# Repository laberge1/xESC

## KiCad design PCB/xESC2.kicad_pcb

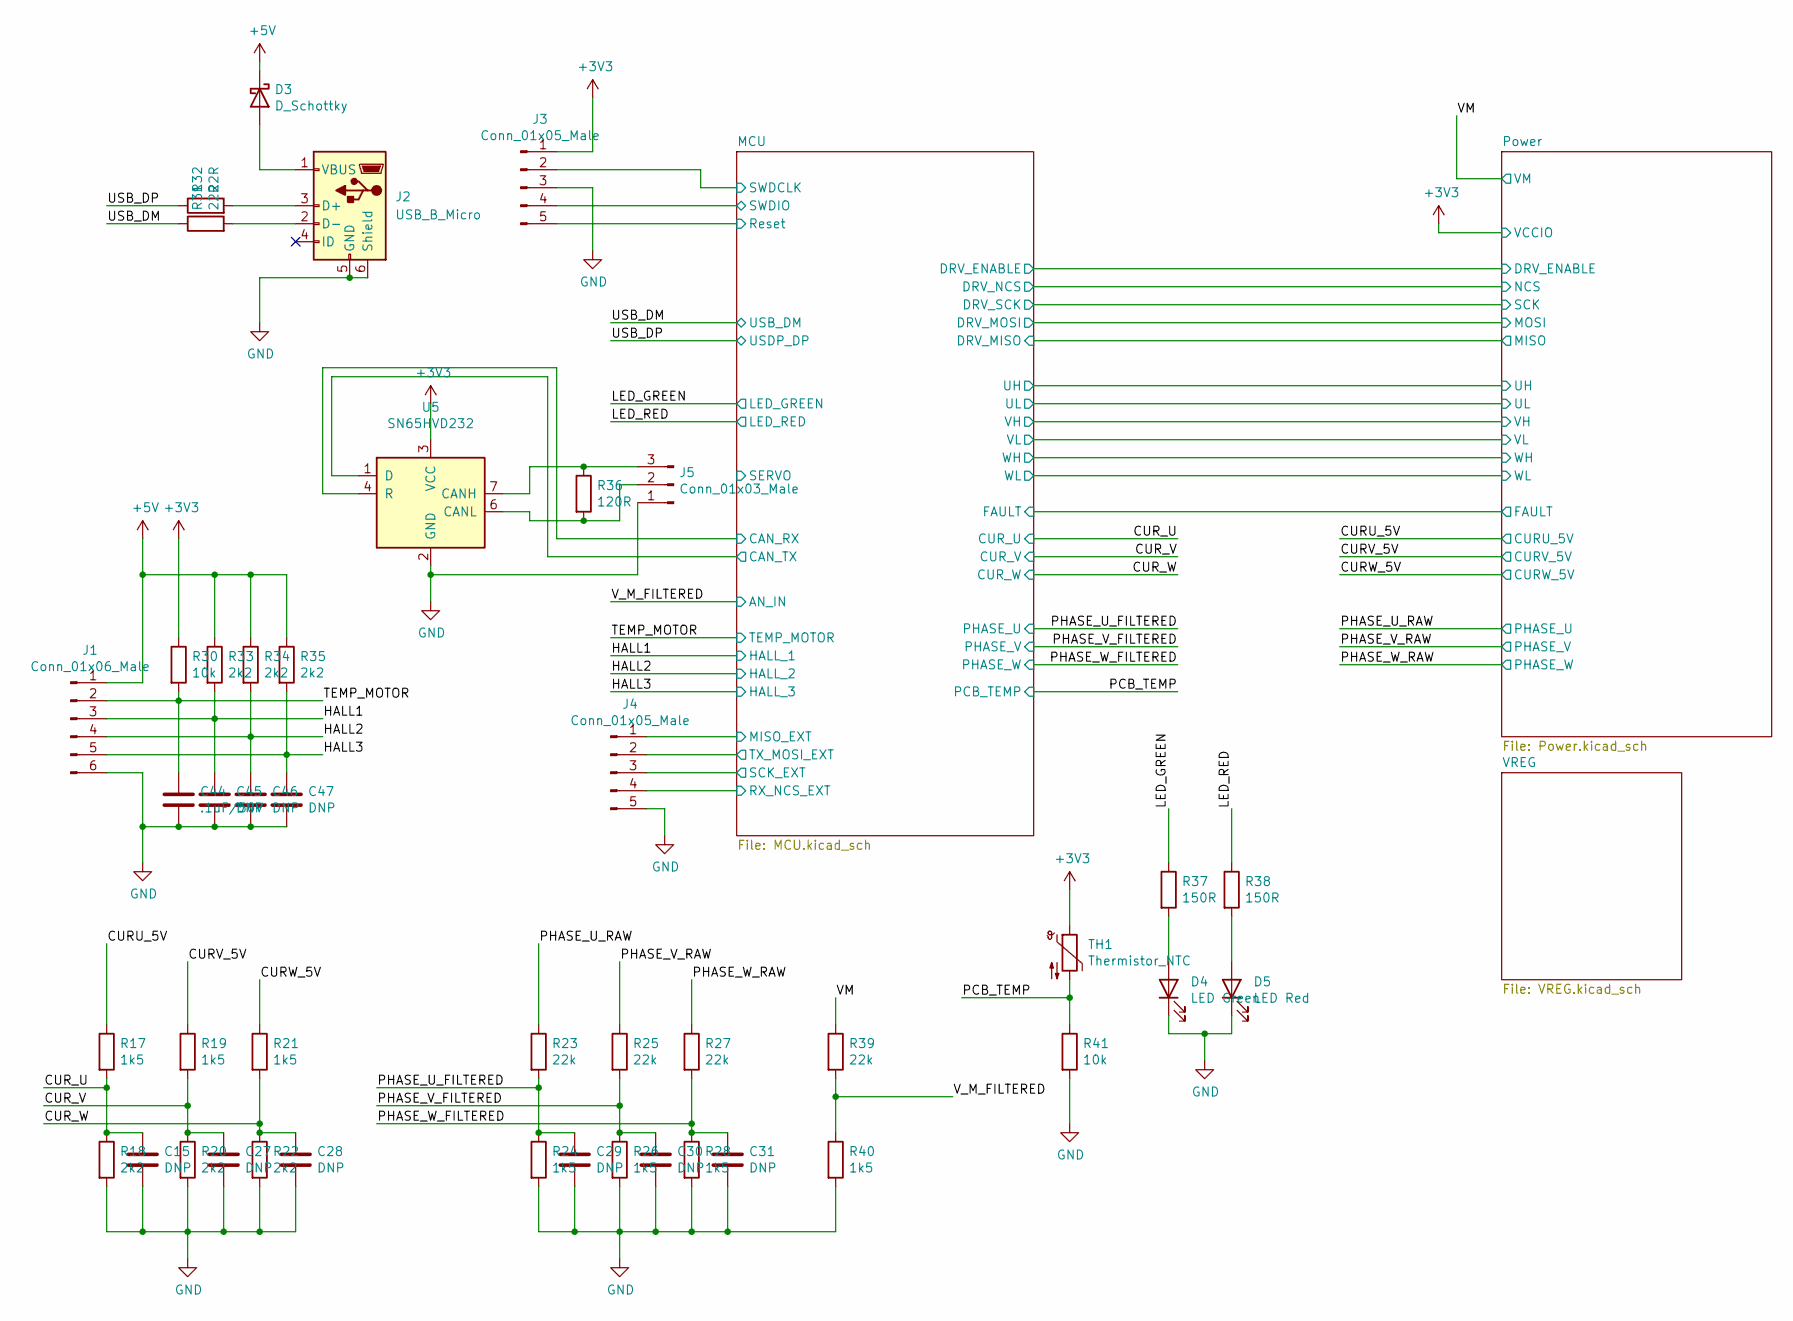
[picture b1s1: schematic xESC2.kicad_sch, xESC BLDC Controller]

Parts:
C15, C27, C28, C29, C30, C31, C45, C46, C47: DNP; C_0603_1608Metric
C44: .1uF/50V; C_0603_1608Metric; Part Number CL10B104KC8NNNC; Digikey 1276-1935-1-ND
D3: D_Schottky; D_SOD-123; Part Number PMEG2010ER,115; Digikey 1727-5192-1-ND
D4: LED Green; LED_0603_1608Metric; Part Number LTST-C191KGKT; Digikey 160-1446-1-ND
D5: LED Red; LED_0603_1608Metric; Part Number LTST-C191KRKT; Digikey 160-1447-1-ND
J1: Conn_01x06_Male; PinHeader_1x06_P2.54mm_Vertical; Part Number DZ254R-11-06-63; LCSC C2935912
J2: USB_B_Micro; USB_Micro; JLC C145795
J3, J4: Conn_01x05_Male; PinHeader_1x05_P2.54mm_Vertical; Part Number DZ254R-11-05-63; LCSC C2935911
J5: Conn_01x03_Male; PinHeader_1x03_P2.54mm_Vertical; Part Number DZ254R-11-05-63; LCSC C2935909
R17, R19, R21, R24, R26, R28, R40: 1k5; R_0603_1608Metric; Part Number RC0603FR-071K5L; Digikey 311-1.50KHRCT-ND
R18, R20, R22, R33, R34, R35: 2k2; R_0603_1608Metric; Part Number RC0603FR-072K2L; Digikey 311-2.20KHRCT-ND
R23, R25, R27, R39: 22k; R_0603_1608Metric; Part Number RMCF0603FT22K0; Digikey RMCF0603FT22K0CT-ND
R30, R41: 10k; R_0603_1608Metric; Part Number RC0603FR-0710KL; Digikey 311-10.0KHRCT-ND
R31, R32: 22R; R_0603_1608Metric; Part Number RMCF0603FT22R0; Digikey RMCF0603FT22R0CT-ND
R36: 120R; R_0603_1608Metric; Part Number RMCF0603FT120R; Digikey RMCF0603FT120RCT-ND
R37, R38: 150R; R_0603_1608Metric; Part Number RC0603FR-07150RL; Digikey 311-150HRCT-ND
TH1: Thermistor_NTC; R_0603_1608Metric; Part Number NCU18XH103F60RB; Digikey 490-16279-1-ND
U5: SN65HVD232; SOIC-8_3.9x4.9mm_P1.27mm; Part Number SN65HVD232; Digikey 296-12282-5-ND

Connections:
+3V3: J3.1, R30.1, TH1.1, U5.3 (VCC); also elsewhere on the board
+5V: D3.1 (K), J1.1, R33.1, R34.1, R35.1; also elsewhere on the board
/CURU_5V: R17.1; also elsewhere on the board
/CURV_5V: R19.1; also elsewhere on the board
/CURW_5V: R21.1; also elsewhere on the board
/CUR_U: C15.1, R17.2, R18.1; also elsewhere on the board
/CUR_V: C27.1, R19.2, R20.1; also elsewhere on the board
/CUR_W: C28.1, R21.2, R22.1; also elsewhere on the board
/HALL1: C45.1, J1.3, R33.2; also elsewhere on the board
/HALL2: C46.1, J1.4, R34.2; also elsewhere on the board
/HALL3: C47.1, J1.5, R35.2; also elsewhere on the board
/LED_GREEN: R37.1; also elsewhere on the board
/LED_RED: R38.1; also elsewhere on the board
/MCU/CAN_RX: U5.4 (R); also elsewhere on the board
/MCU/CAN_TX: U5.1 (D); also elsewhere on the board
/MCU/MISO_EXT: J4.1; also elsewhere on the board
/MCU/RX_NCS_EXT: J4.4; also elsewhere on the board
/MCU/Reset: J3.5; also elsewhere on the board
/MCU/SCK_EXT: J4.3; also elsewhere on the board
/MCU/SWDCLK: J3.2; also elsewhere on the board
/MCU/SWDIO: J3.4; also elsewhere on the board
/MCU/TX_MOSI_EXT: J4.2; also elsewhere on the board
/PCB_TEMP: R41.1, TH1.2; also elsewhere on the board
/PHASE_U_FILTERED: C29.1, R23.2, R24.1; also elsewhere on the board
/PHASE_U_RAW: R23.1; also elsewhere on the board
/PHASE_V_FILTERED: C30.1, R25.2, R26.1; also elsewhere on the board
/PHASE_V_RAW: R25.1; also elsewhere on the board
/PHASE_W_FILTERED: C31.1, R27.2, R28.1; also elsewhere on the board
/PHASE_W_RAW: R27.1; also elsewhere on the board
/TEMP_MOTOR: C44.1, J1.2, R30.2; also elsewhere on the board
/USB_DM: R31.1; also elsewhere on the board
/USB_DP: R32.1; also elsewhere on the board
/VM: R39.1; also elsewhere on the board
/V_M_FILTERED: R39.2, R40.1; also elsewhere on the board
GND: C15.2, C27.2, C28.2, C29.2, C30.2, C31.2, C44.2, C45.2, C46.2, C47.2, D4.1 (K), D5.1 (K), J1.6, J2.5 (GND), J2.6 (Shield), J3.3, J4.5, J5.1, R18.2, R20.2, R22.2, R24.2, R26.2, R28.2, R40.2, R41.2, U5.2 (GND); also elsewhere on the board
unnamed: D3.2 (A), J2.1 (VBUS)
unnamed: D4.2 (A), R37.2
unnamed: D5.2 (A), R38.2
unnamed: J2.3 (D+), R32.2
unnamed: J2.2 (D-), R31.2
unnamed: J5.2, R36.2, U5.6 (CANL)
unnamed: J5.3, R36.1, U5.7 (CANH)

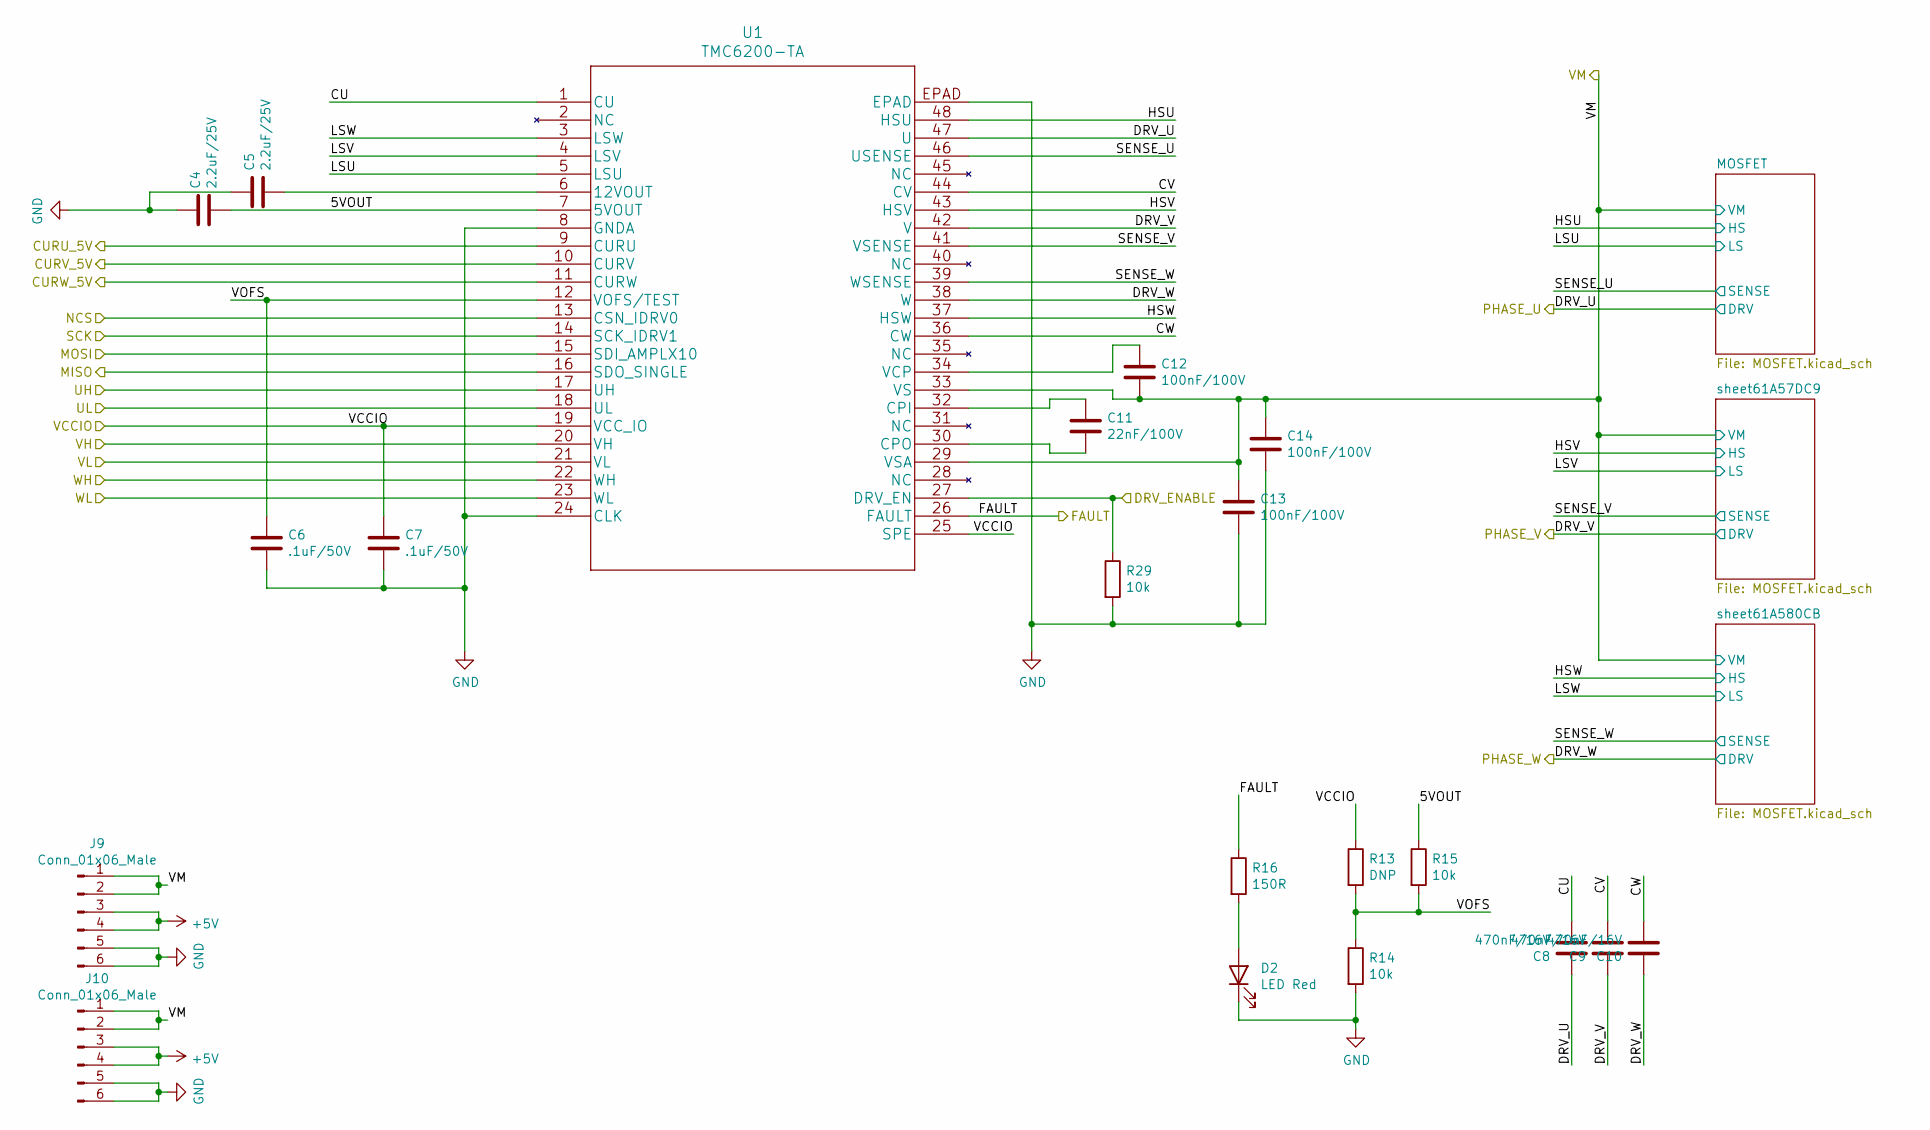
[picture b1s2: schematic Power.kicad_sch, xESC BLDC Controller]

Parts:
C4, C5: 2.2uF/25V; C_0805_2012Metric; Part Number GRM21BR71E225KE11L; Digikey 490-14467-1-ND
C6, C7: .1uF/50V; C_0603_1608Metric; Part Number CL10B104KC8NNNC; Digikey 1276-1935-1-ND
C8, C9, C10: 470nF/16V; C_0603_1608Metric; Part Number CL10B474KO8NNNC; Digikey 1276-1062-1-ND
C11: 22nF/100V; C_0603_1608Metric; Part Number C0603C223K1RAC7867; Digikey 399-C0603C223K1RAC7867CT-ND
C12, C13, C14: 100nF/100V; C_0805_2012Metric; Part Number HMK212BJ104KG-T; JLC C28233
D2: LED Red; LED_0603_1608Metric; Part Number LTST-C191KRKT; Digikey 160-1447-1-ND
J9, J10: Conn_01x06_Male; PinHeader_1x06_P2.54mm_Vertical; Part Number DZ254R-11-06-63; LCSC C2935912
R13: DNP; R_0603_1608Metric
R14, R15, R29: 10k; R_0603_1608Metric; Part Number RC0603FR-0710KL; Digikey 311-10.0KHRCT-ND
R16: 150R; R_0603_1608Metric; Part Number RC0603FR-07150RL; Digikey 311-150HRCT-ND
U1: TMC6200-TA; Part Number TMC6200-TA; Digikey 1460-1384-ND

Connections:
+3V3: C7.1, R13.1, U1.19 (VCC_IO), U1.25 (SPE); also elsewhere on the board
+5V: J9.3, J9.4, J10.3, J10.4; also elsewhere on the board
/CURU_5V: U1.9 (CURU); also elsewhere on the board
/CURV_5V: U1.10 (CURV); also elsewhere on the board
/CURW_5V: U1.11 (CURW); also elsewhere on the board
/MCU/DRV_ENABLE: R29.1, U1.27 (DRV_EN); also elsewhere on the board
/MCU/DRV_MISO: U1.16 (SDO_SINGLE); also elsewhere on the board
/MCU/DRV_MOSI: U1.15 (SDI_AMPLX10); also elsewhere on the board
/MCU/DRV_NCS: U1.13 (CSN_IDRV0); also elsewhere on the board
/MCU/DRV_SCK: U1.14 (SCK_IDRV1); also elsewhere on the board
/MCU/UH: U1.17 (UH); also elsewhere on the board
/MCU/UL: U1.18 (UL); also elsewhere on the board
/MCU/VH: U1.20 (VH); also elsewhere on the board
/MCU/VL: U1.21 (VL); also elsewhere on the board
/MCU/WH: U1.22 (WH); also elsewhere on the board
/MCU/WL: U1.23 (WL); also elsewhere on the board
/PHASE_U_RAW: C8.1, U1.47 (U); also elsewhere on the board
/PHASE_V_RAW: C9.1, U1.42 (V); also elsewhere on the board
/PHASE_W_RAW: C10.1, U1.38 (W); also elsewhere on the board
/Power/5VOUT: C4.2, R15.1, U1.7 (5VOUT)
/Power/CU: C8.2, U1.1 (CU)
/Power/CV: C9.2, U1.44 (CV)
/Power/CW: C10.2, U1.36 (CW)
/Power/FAULT: R16.1, U1.26 (FAULT); also elsewhere on the board
/Power/HSU: U1.48 (HSU); also elsewhere on the board
/Power/HSV: U1.43 (HSV); also elsewhere on the board
/Power/HSW: U1.37 (HSW); also elsewhere on the board
/Power/LSU: U1.5 (LSU); also elsewhere on the board
/Power/LSV: U1.4 (LSV); also elsewhere on the board
/Power/LSW: U1.3 (LSW); also elsewhere on the board
/Power/SENSE_U: U1.46 (USENSE); also elsewhere on the board
/Power/SENSE_V: U1.41 (VSENSE); also elsewhere on the board
/Power/SENSE_W: U1.39 (WSENSE); also elsewhere on the board
/Power/VOFS: C6.1, R13.2, R14.1, R15.2, U1.12 (VOFS/TEST)
/VM: C12.2, C13.1, C14.1, J9.1, J9.2, J10.1, J10.2, U1.29 (VSA), U1.33 (VS); also elsewhere on the board
GND: C4.1, C5.1, C6.2, C7.2, C13.2, C14.2, D2.1 (K), J9.5, J9.6, J10.5, J10.6, R14.2, R29.2, U1.8 (GNDA), U1.24 (CLK), U1.EPAD; also elsewhere on the board
unnamed: D2.2 (A), R16.2
unnamed: C5.2, U1.6 (12VOUT)
unnamed: C11.2, U1.32 (CPI)
unnamed: C11.1, U1.30 (CPO)
unnamed: C12.1, U1.34 (VCP)

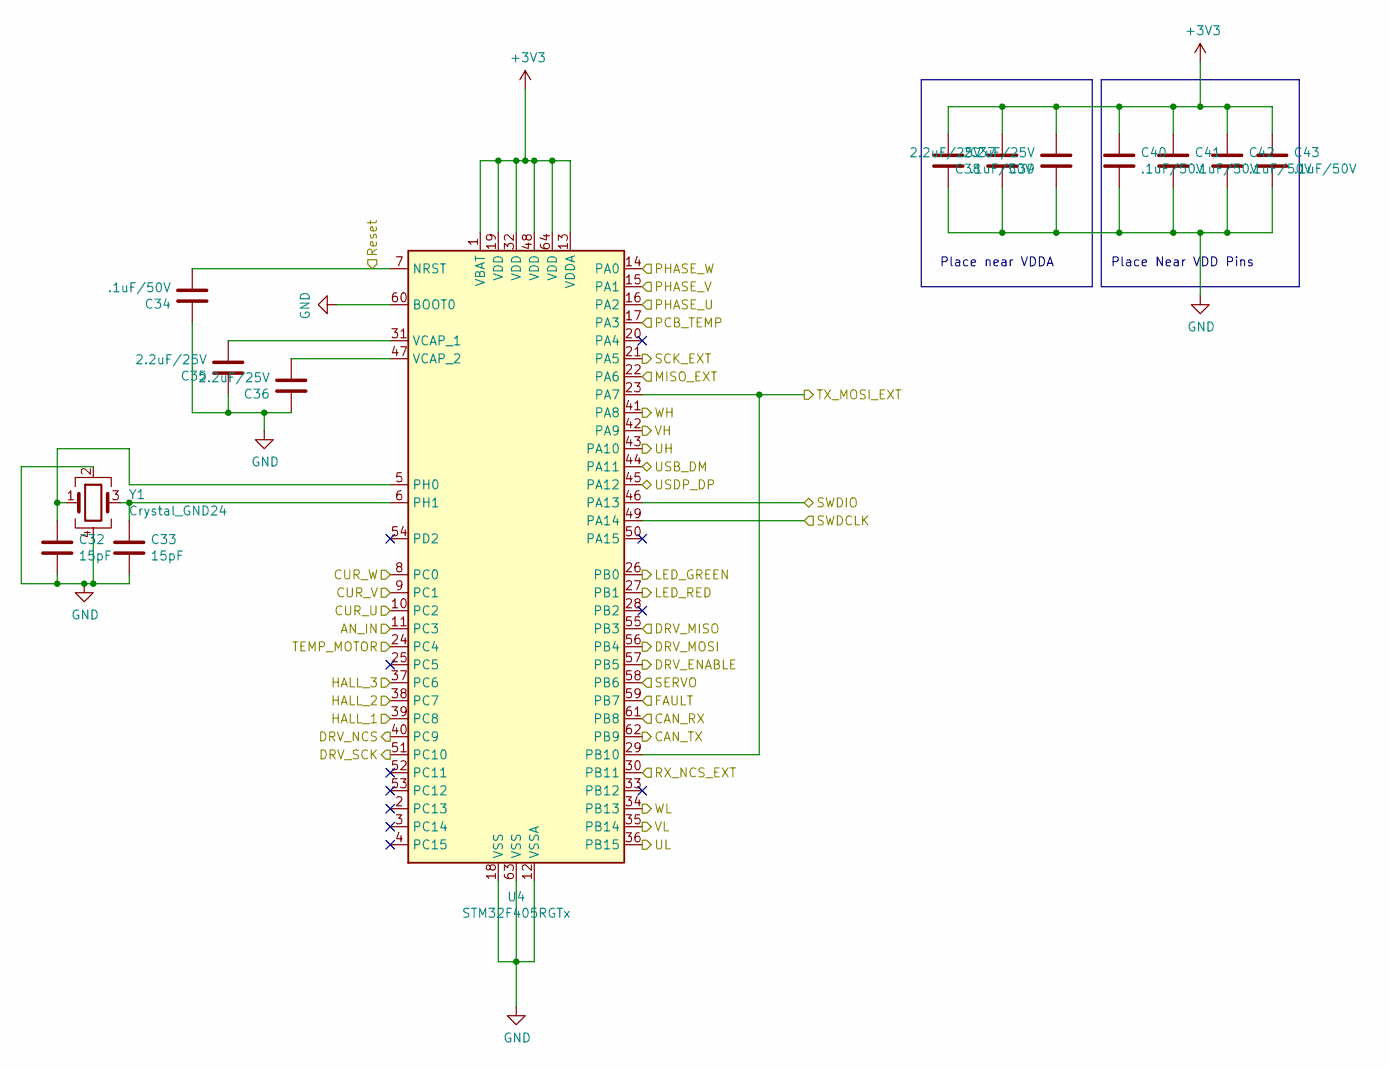
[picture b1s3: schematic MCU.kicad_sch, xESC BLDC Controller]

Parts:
C32, C33: 15pF; C_0603_1608Metric; Part Number GRM1885C2A150JA01D; Digikey 490-1331-1-ND
C34, C37, C40, C41, C42, C43: .1uF/50V; C_0603_1608Metric; Part Number CL10B104KC8NNNC; Digikey 1276-1935-1-ND
C35, C36, C38, C39: 2.2uF/25V; C_0805_2012Metric; Part Number GRM21BR71E225KE11L; Digikey 490-14467-1-ND
U4: STM32F405RGTx; LQFP-64_10x10mm_P0.5mm; Part Number STM32F405RGTx; LCSC C15742
Y1: Crystal_GND24; Crystal_SMD_3225-4Pin_3.2x2.5mm; Part Number ECS-80-12-33-JGN-TR; Digikey 50-ECS-80-12-33-JGN-CT-ND

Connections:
+3V3: C37.1, C38.2, C39.2, C40.1, C41.1, C42.1, C43.1, U4.1 (VBAT), U4.13 (VDDA), U4.19 (VDD), U4.32 (VDD), U4.48 (VDD), U4.64 (VDD); also elsewhere on the board
/CUR_U: U4.10 (PC2); also elsewhere on the board
/CUR_V: U4.9 (PC1); also elsewhere on the board
/CUR_W: U4.8 (PC0); also elsewhere on the board
/HALL1: U4.39 (PC8); also elsewhere on the board
/HALL2: U4.38 (PC7); also elsewhere on the board
/HALL3: U4.37 (PC6); also elsewhere on the board
/LED_GREEN: U4.26 (PB0); also elsewhere on the board
/LED_RED: U4.27 (PB1); also elsewhere on the board
/MCU/CAN_RX: U4.61 (PB8); also elsewhere on the board
/MCU/CAN_TX: U4.62 (PB9); also elsewhere on the board
/MCU/DRV_ENABLE: U4.57 (PB5); also elsewhere on the board
/MCU/DRV_MISO: U4.55 (PB3); also elsewhere on the board
/MCU/DRV_MOSI: U4.56 (PB4); also elsewhere on the board
/MCU/DRV_NCS: U4.40 (PC9); also elsewhere on the board
/MCU/DRV_SCK: U4.51 (PC10); also elsewhere on the board
/MCU/MISO_EXT: U4.22 (PA6); also elsewhere on the board
/MCU/RX_NCS_EXT: U4.30 (PB11); also elsewhere on the board
/MCU/Reset: C34.2, U4.7 (NRST); also elsewhere on the board
/MCU/SCK_EXT: U4.21 (PA5); also elsewhere on the board
/MCU/SERVO: U4.58 (PB6)
/MCU/SWDCLK: U4.49 (PA14); also elsewhere on the board
/MCU/SWDIO: U4.46 (PA13); also elsewhere on the board
/MCU/TX_MOSI_EXT: U4.23 (PA7), U4.29 (PB10); also elsewhere on the board
/MCU/UH: U4.43 (PA10); also elsewhere on the board
/MCU/UL: U4.36 (PB15); also elsewhere on the board
/MCU/VH: U4.42 (PA9); also elsewhere on the board
/MCU/VL: U4.35 (PB14); also elsewhere on the board
/MCU/WH: U4.41 (PA8); also elsewhere on the board
/MCU/WL: U4.34 (PB13); also elsewhere on the board
/PCB_TEMP: U4.17 (PA3); also elsewhere on the board
/PHASE_U_FILTERED: U4.16 (PA2); also elsewhere on the board
/PHASE_V_FILTERED: U4.15 (PA1); also elsewhere on the board
/PHASE_W_FILTERED: U4.14 (PA0); also elsewhere on the board
/Power/FAULT: U4.59 (PB7); also elsewhere on the board
/TEMP_MOTOR: U4.24 (PC4); also elsewhere on the board
/USB_DM: U4.44 (PA11); also elsewhere on the board
/USB_DP: U4.45 (PA12); also elsewhere on the board
/V_M_FILTERED: U4.11 (PC3); also elsewhere on the board
GND: C32.2, C33.2, C34.1, C35.1, C36.1, C37.2, C38.1, C39.1, C40.2, C41.2, C42.2, C43.2, U4.12 (VSSA), U4.18 (VSS), U4.60 (BOOT0), U4.63 (VSS), Y1.2, Y1.4; also elsewhere on the board
unnamed: C32.1, U4.5 (PH0), Y1.1
unnamed: C33.1, U4.6 (PH1), Y1.3
unnamed: C35.2, U4.31 (VCAP_1)
unnamed: C36.2, U4.47 (VCAP_2)

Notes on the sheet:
Place Near VDD Pins
Place near VDDA

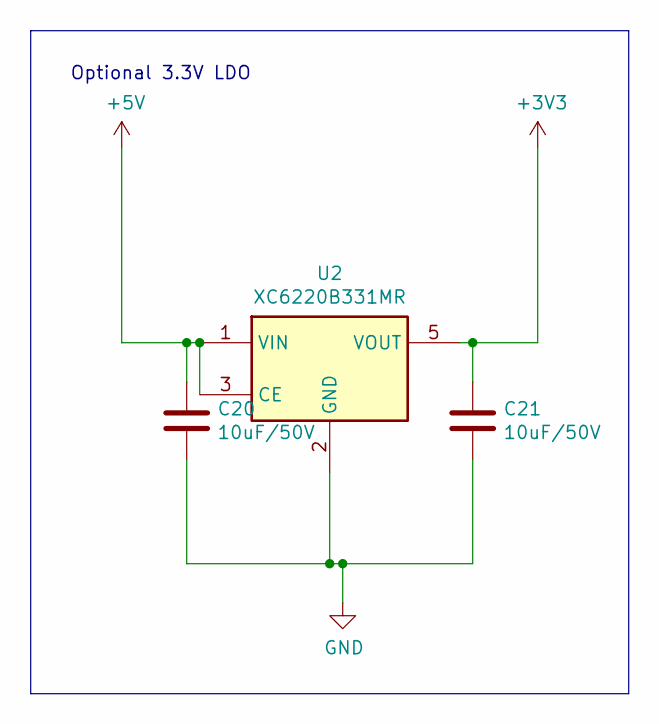
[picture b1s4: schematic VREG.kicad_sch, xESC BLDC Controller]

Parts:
C20, C21: 10uF/50V; C_1206_3216Metric; Part Number CL31A106KAHNNNE; Digikey 1276-1075-1-ND
U2: XC6220B331MR; SOT-23-5; Part Number XC6220B331MR; Digikey 893-1133-1-ND

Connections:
+3V3: C21.1, U2.5 (VOUT); also elsewhere on the board
+5V: C20.1, U2.1 (VIN), U2.3 (CE); also elsewhere on the board
GND: C20.2, C21.2, U2.2 (GND); also elsewhere on the board

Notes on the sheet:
Optional 3.3V LDO

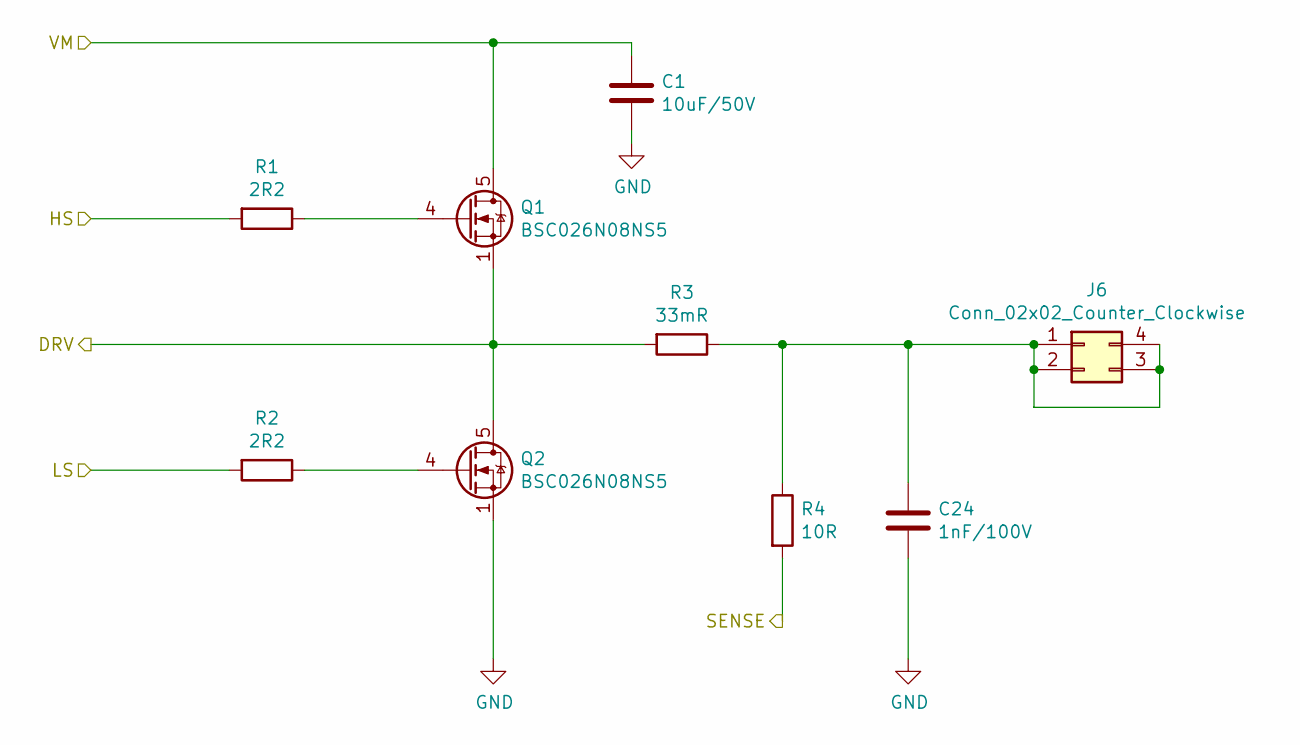
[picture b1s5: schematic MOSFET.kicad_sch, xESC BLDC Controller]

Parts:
C1: 10uF/50V; C_1206_3216Metric; Part Number CL31B225KBHVPNE; Digikey 1276-6735-1-ND
C24: 1nF/100V; C_0603_1608Metric; Part Number GCM188R72A102KA37D; Digikey 490-4780-1-ND
J6: Conn_02x02_Counter_Clockwise; PinHeader_2x02_P2.54mm_Vertical; Part Number B-2100S04P-B110; LCSC C124362
Q1, Q2: BSC026N08NS5; TDSON-8-1; Part Number BSC026N08NS5; Digikey BSC026N08NS5ATMA1CT-ND
R1, R2: 2R2; R_0603_1608Metric; Part Number ERJ-3GEYJ2R2V; Digikey P2.2GCT-ND
R3: 33mR; R_2512_6332Metric; Part Number ARP2512GJR033; LCSC C2903495
R4: 10R; R_0603_1608Metric; Part Number RMCF0603FT10R0; Digikey RMCF0603FT10R0CT-ND

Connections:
/PHASE_U_RAW: Q1.1 (S), Q1.2 (S), Q1.3 (S), Q2.5 (D), R3.2; also elsewhere on the board
/Power/HSU: R1.2; also elsewhere on the board
/Power/LSU: R2.2; also elsewhere on the board
/Power/SENSE_U: R4.2; also elsewhere on the board
/VM: C1.1, Q1.5 (D); also elsewhere on the board
GND: C1.2, C24.2, Q2.1 (S), Q2.2 (S), Q2.3 (S); also elsewhere on the board
unnamed: C24.1, J6.1, J6.2, J6.3, J6.4, R3.1, R4.1
unnamed: Q1.4 (G), R1.1
unnamed: Q2.4 (G), R2.1

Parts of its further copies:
C2, C3: 10uF/50V; C_1206_3216Metric; Part Number CL31B225KBHVPNE; Digikey 1276-6735-1-ND
C25, C26: 1nF/100V; C_0603_1608Metric; Part Number GCM188R72A102KA37D; Digikey 490-4780-1-ND
J7, J8: Conn_02x02_Counter_Clockwise; PinHeader_2x02_P2.54mm_Vertical; Part Number B-2100S04P-B110; LCSC C124362
Q3, Q4, Q5, Q6: BSC026N08NS5; TDSON-8-1; Part Number BSC026N08NS5; Digikey BSC026N08NS5ATMA1CT-ND
R5, R6, R9, R10: 2R2; R_0603_1608Metric; Part Number ERJ-3GEYJ2R2V; Digikey P2.2GCT-ND
R7, R11: 33mR; R_2512_6332Metric; Part Number ARP2512GJR033; LCSC C2903495
R8, R12: 10R; R_0603_1608Metric; Part Number RMCF0603FT10R0; Digikey RMCF0603FT10R0CT-ND

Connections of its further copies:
/PHASE_V_RAW: Q3.1 (S), Q3.2 (S), Q3.3 (S), Q4.5 (D), R7.2; also elsewhere on the board
/PHASE_W_RAW: Q5.1 (S), Q5.2 (S), Q5.3 (S), Q6.5 (D), R11.2; also elsewhere on the board
/Power/HSV: R5.2; also elsewhere on the board
/Power/HSW: R9.2; also elsewhere on the board
/Power/LSV: R6.2; also elsewhere on the board
/Power/LSW: R10.2; also elsewhere on the board
/Power/SENSE_V: R8.2; also elsewhere on the board
/Power/SENSE_W: R12.2; also elsewhere on the board
/VM: C2.1, C3.1, Q3.5 (D), Q5.5 (D); also elsewhere on the board
GND: C2.2, C3.2, C25.2, C26.2, Q4.1 (S), Q4.2 (S), Q4.3 (S), Q6.1 (S), Q6.2 (S), Q6.3 (S); also elsewhere on the board
unnamed: C25.1, J7.1, J7.2, J7.3, J7.4, R7.1, R8.1
unnamed: C26.1, J8.1, J8.2, J8.3, J8.4, R11.1, R12.1
unnamed: Q3.4 (G), R5.1
unnamed: Q4.4 (G), R6.1
unnamed: Q5.4 (G), R9.1
unnamed: Q6.4 (G), R10.1

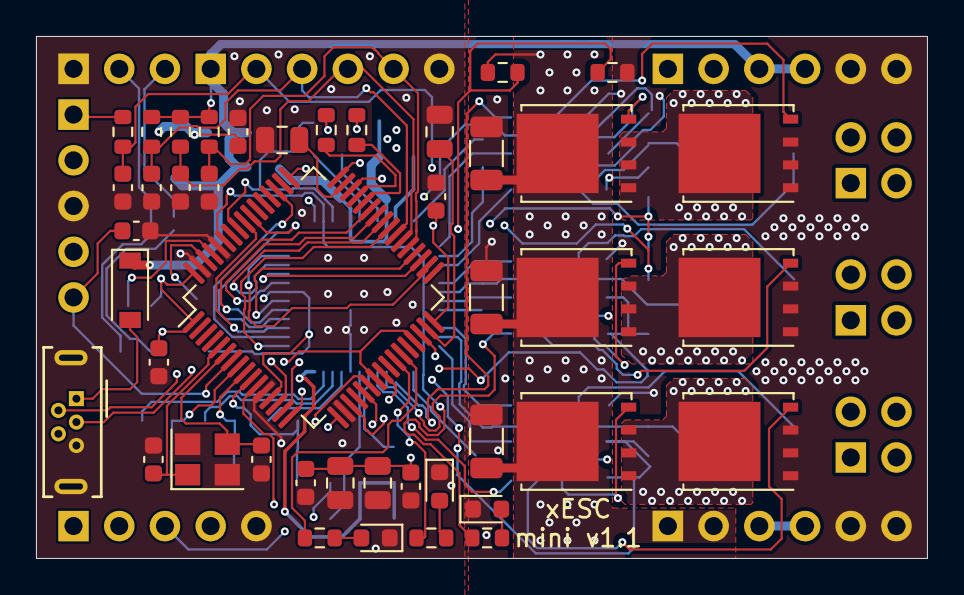
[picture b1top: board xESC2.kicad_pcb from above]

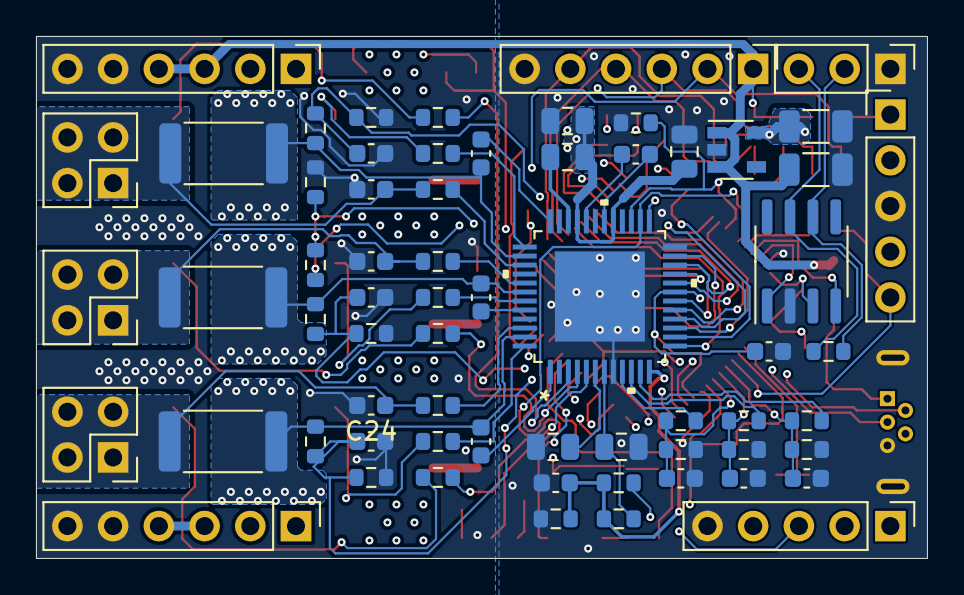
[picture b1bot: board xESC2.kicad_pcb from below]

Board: 4 copper layers, 49.5 x 29.0 mm, 108 parts (65 on the bottom side), 86 nets.

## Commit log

2025-12-31 Updated to kicad v9
2025-12-31 Updated pcb file to v9 and ran html bom

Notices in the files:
PCB/MCU.kicad_sch:
Creative Commons Attribution-NonCommercial-ShareAlike 4.0 International License.
Licensed under
parts and their libraries:
Copyright 2021 Accelerated Designs. All rights reserved.
